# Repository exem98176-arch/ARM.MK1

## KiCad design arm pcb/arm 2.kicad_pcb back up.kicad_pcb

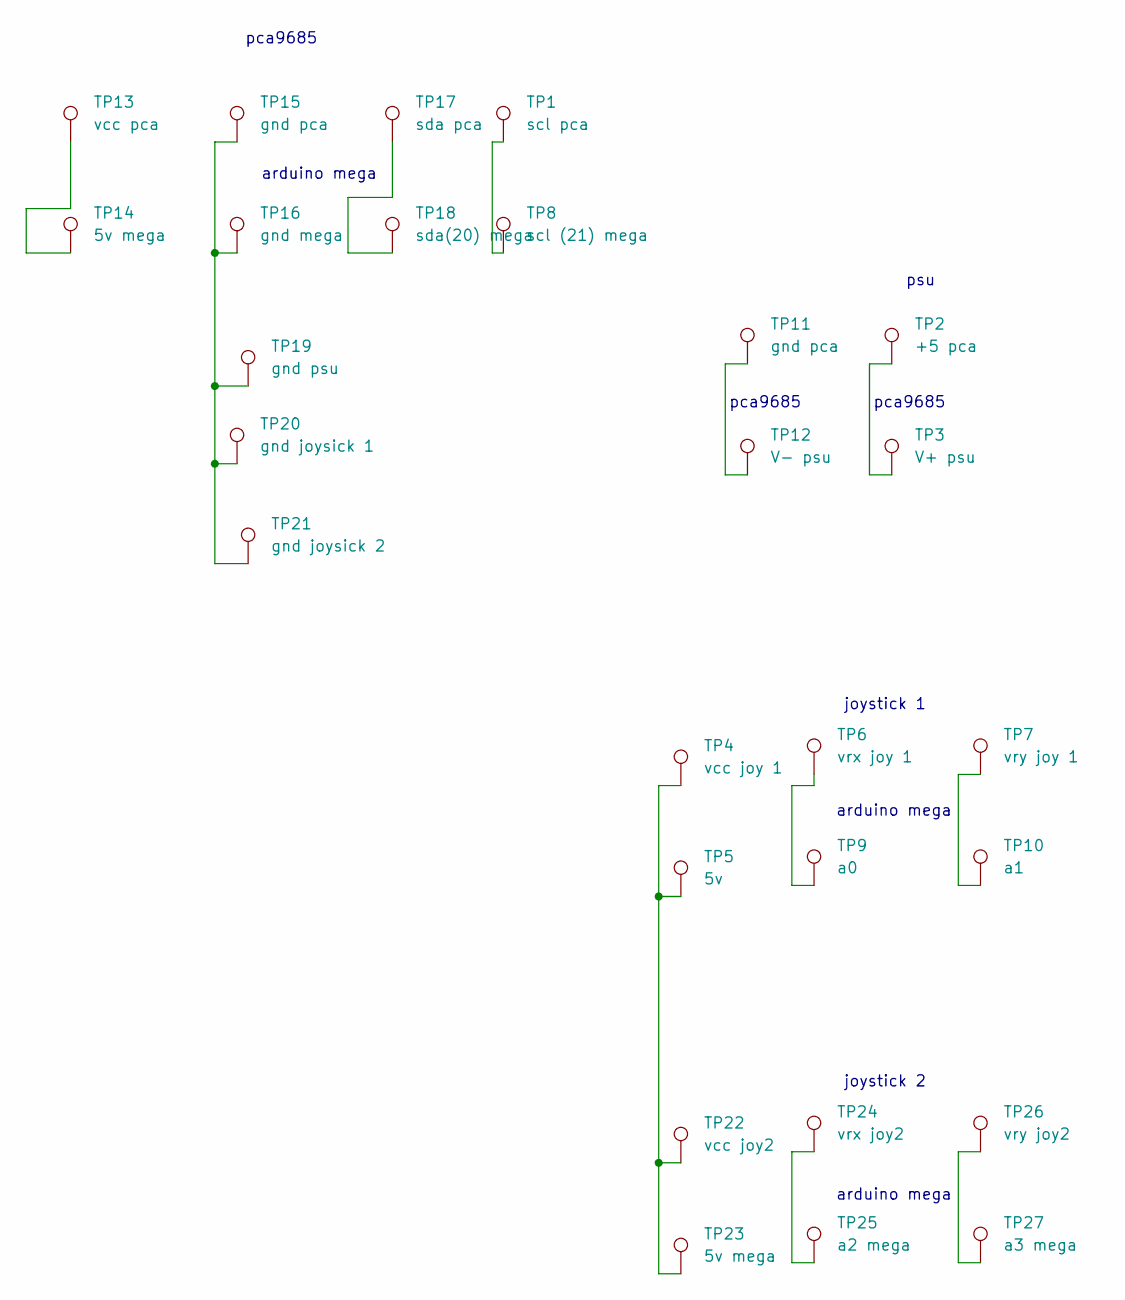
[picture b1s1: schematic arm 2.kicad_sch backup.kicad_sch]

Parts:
TP1: scl pca; TestPoint_THTPad_D1.5mm_Drill0.7mm
TP2: +5 pca; TestPoint_THTPad_D1.5mm_Drill0.7mm
TP3: V+ psu; TestPoint_THTPad_D1.5mm_Drill0.7mm
TP4: vcc joy 1; TestPoint_THTPad_D1.5mm_Drill0.7mm
TP5: 5v; TestPoint_THTPad_D1.5mm_Drill0.7mm
TP6: vrx joy 1; TestPoint_THTPad_D1.5mm_Drill0.7mm
TP7: vry joy 1; TestPoint_THTPad_D1.5mm_Drill0.7mm
TP8: scl (21) mega; TestPoint_THTPad_D1.5mm_Drill0.7mm
TP9: a0; TestPoint_THTPad_D1.5mm_Drill0.7mm
TP10: a1; TestPoint_THTPad_D1.5mm_Drill0.7mm
TP11, TP15: gnd pca; TestPoint_THTPad_D1.5mm_Drill0.7mm
TP12: V- psu; TestPoint_THTPad_D1.5mm_Drill0.7mm
TP13: vcc pca; TestPoint_THTPad_D1.5mm_Drill0.7mm
TP14, TP23: 5v mega; TestPoint_THTPad_D1.5mm_Drill0.7mm
TP16: gnd mega; TestPoint_THTPad_D1.5mm_Drill0.7mm
TP17: sda pca; TestPoint_THTPad_D1.5mm_Drill0.7mm
TP18: sda(20) mega; TestPoint_THTPad_D1.5mm_Drill0.7mm
TP19: gnd psu; TestPoint_THTPad_D1.5mm_Drill0.7mm
TP20: gnd joysick 1; TestPoint_THTPad_D1.5mm_Drill0.7mm
TP21: gnd joysick 2; TestPoint_THTPad_D1.5mm_Drill0.7mm
TP22: vcc joy2; TestPoint_THTPad_D1.5mm_Drill0.7mm
TP24: vrx joy2; TestPoint_THTPad_D1.5mm_Drill0.7mm
TP25: a2 mega; TestPoint_THTPad_D1.5mm_Drill0.7mm
TP26: vry joy2; TestPoint_THTPad_D1.5mm_Drill0.7mm
TP27: a3 mega; TestPoint_THTPad_D1.5mm_Drill0.7mm

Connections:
unnamed: TP1.1 (1_1), TP8.1 (1_1)
unnamed: TP2.1 (1_1), TP3.1 (1_1)
unnamed: TP6.1 (1_1), TP9.1 (1_1)
unnamed: TP7.1 (1_1), TP10.1 (1_1)
unnamed: TP11.1 (1_1), TP12.1 (1_1)
unnamed: TP13.1 (1_1), TP14.1 (1_1)
unnamed: TP15.1 (1_1), TP16.1 (1_1), TP19.1 (1_1), TP20.1 (1_1), TP21.1 (1_1)
unnamed: TP17.1 (1_1), TP18.1 (1_1)
unnamed: TP4.1 (1_1), TP5.1 (1_1), TP22.1 (1_1), TP23.1 (1_1)
unnamed: TP24.1 (1_1), TP25.1 (1_1)
unnamed: TP26.1 (1_1), TP27.1 (1_1)

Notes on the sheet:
psu
joystick 1
arduino mega
joystick 2
pca9685

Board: 2 copper layers, 27 parts (0 on the bottom side), 11 nets, no tracks yet.
